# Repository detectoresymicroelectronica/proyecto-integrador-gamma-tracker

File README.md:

# Gamma Tracker
### Sonda gamma para cirugía radioguiada

<p>
Sistema de detección de radiación gamma para asistencia en cirugía laparoscópica oncológica, basado en <strong>centellador inorgánico + SiPM</strong>, con electrónica de lectura multicanal e interfaz en tiempo real.
</p>

<hr>

<p>
<strong>PROYECTO INTEGRADOR</strong><br>
Ingeniería en Telecomunicaciones · Instituto Balseiro · 2026–2027
</p>

<p>
<strong>Autor:</strong> Dana E. González<br>
<strong>Director:</strong> José Lipovetzky<br>
<strong>Codirector:</strong> Fabricio Alcalde
</p>

---

## Contexto

Este proyecto continúa y extiende el trabajo de la tesis *Gamma Tracker* (Torletti, 2025), que demostró la viabilidad de una sonda gamma portátil basada en centellador + SiPM para localización de tejido tumoral marcado con FDG (TRL 4–5). El dispositivo se encuentra en proceso de patentamiento ante el INPI.

El presente proyecto integrador busca avanzar hacia un sistema de mayor resolución espacial y espectral, abordando cuatro líneas principales:

* **Nuevo fotosensor:** evaluación de SiPMs de mayor área activa y menor tensión de polarización, con capacidad de espectroscopía de altura de pulso para discriminación energética a 511 keV.
* **Acople óptico:** comparación cuantitativa de técnicas (grasa óptica, adhesivos UV, fibra óptica) para optimizar eficiencia de transferencia de luz y estabilidad mecánica.
* **Sistema multipixel:** diseño de una matriz de centelladores acoplados a un arreglo de SiPMs con lectura multicanal para mapeo espacial de actividad gamma en tiempo real.
* **Electrónica e interfaz:** desarrollo de electrónica de adquisición, comunicación inalámbrica y alimentación por baterías, aptas para entorno quirúrgico (objetivo TRL 5–6).

---

## Estructura del repositorio

```text
logs/               Cuaderno de laboratorio digital (un archivo por sesión) + criterios/guias/instrucciones
scripts/
  ├── read/         Control de instrumentos y lectura
  └── analysis/     Post-procesamiento, comparación y visualización
data/               Datos experimentales organizados por campaña
  └── <campaña>/
      ├── raw/      CSV crudos (inmutables)
      └── graphs/   Curvas de los resultados
hardware/           Diseños de PCB (KiCad), uno por placa
  └── EVB-TIA-v0/
      └── fab/      Archivos de fabricación enviados (Gerber, BOM, CPL)
docs/               Documentación de soporte e imágenes de los logs
```

## 📓 Cuaderno de laboratorio

> El directorio `logs/` funciona como **cuaderno de laboratorio digital** del proyecto. Cada archivo registra una sesión de trabajo con objetivo, configuración experimental, observaciones, resultados, decisiones técnicas y pendientes. Tambien se incluyen documentos que sustenten las decisiones experimentales.
>
> Los logs priorizan **trazabilidad y reproducibilidad** por sobre presentación. Todo se registra en el cuaderno, preservando el historial completo del razonamiento experimental. 
>
> ```
> logs/
>  ├── 1 LOG — Lunes 3 de agosto de 2026.md
>  ├── 2 LOG — Lunes 10 de agosto de 2026.md
>  └── ...
> ```

---

## Progreso del proyecto

### Hitos

- **Hito 1 — Validación de SiPMs MICROFC-60035-SMT** (11/08/2026) — dispersión de V_br intra-lote σ ≈ 20 mV, ~100× menor que el modelo del prototipo anterior. Los 10 dispositivos son aptos para la matriz multipixel. Habilita la primera propuesta del PI.
- **Hito 2 — Primeros pulsos de fotón individual** (09/09/2026) — dark counts observados con la placa amplificadora BGA614 ×100 (SiPM #09). Primera vez que la cadena SiPM → amplificador → osciloscopio funciona en el proyecto.
- **Hito 3 — EVB-TIA v0 enviada a fabricar** (20/10/2026) — primera placa propia: TIA de una etapa con ADA4895 sobre la salida estándar del SiPM, con banco de R_F configurable por jumpers (159 Ω – 2,2 kΩ). 5 placas ensambladas en JLCPCB, con el SiPM soldado por reflujo.

### Registro semanal

**Semana del 03/08/2026**
- Setup de medición I-V validado (Keithley 2450 + pyvisa + script Python)
- Protocolo de conexión y seguridad definido 

**Semana del 10/08/2026**
- Caracterización I-V de los 10 SiPMs completada 
- Se confirmó offset de V_br entre lotes (~141 mV) 
- **→ Hito 1 alcanzado**

**Semana del 17/08/2026**
- Primer diseño en KiCad: placa breakout para el SiPM (fresada en CNC)

**Semana del 24/08/2026**
- Corriente oscura de los 10 SiPMs a V_ov = 2,5 V
- Plan del banco térmico (Peltier + watercooling + DS18B20)
- SiPM #05 destruido al soldarlo → protocolo de soldadura (≤ 260 °C, ≤ 10 s)

**Semana del 31/08/2026**
- Demostrado que el 60035 no se puede leer sin amplificación (3400 pF → ~0,14 mV/PE)

**Semana del 07/09/2026**
- Pulsos de fotón individual con la placa BGA614 ×100
- **→ Hito 2 alcanzado**

**Semana del 14/09/2026**
- Arduino + DS18B20 validado; Peltier nueva probada
- Comparación de topologías de amplificación (BGA614, TIA, amplificador inversor)

**Semana del 21/09/2026**
- Simulación del TIA de una etapa (ADA4895, Configuración C) y definición del banco de R_F

**Semanas del 05/10 y 12/10/2026**
- Diseño de la EVB-TIA v0 en KiCad: esquemático, layout, plano de masa, serigrafía (DRC 0/0/0)

**Semana del 19/10/2026**
- Archivos de fabricación y pedido a JLCPCB
- **→ Hito 3 alcanzado**

**Semana del 26/10/2026** *(próxima)*
- Banco térmico: reparar el conmutador de la Peltier y medir dV_br/dT
- Preparar la cadena de medición para la EVB-TIA (adquisición con osciloscopio, análisis de SPE)

---

## Convenciones

**Datos:** `{modelo}_{numero}_{YYYYMMDD}.csv`<br>
**Logs:** `N LOG — Día D de mes de AAAA.md`<br>
**Dispositivos:** `MFC60035_XX` (numeración secuencial por orden de medición)

---

## Instrumentación

| Equipo              | Modelo                                      | Interfaz              |
| ------------------- | ------------------------------------------- | --------------------- |
| Source Measure Unit | Keithley 2450                               | USB / SCPI vía PyVISA |
| Osciloscopio        | Keysight InfiniiVision DSOX3104T (1 GHz)    | —                     |
| Osciloscopio        | Rigol DS1204B (200 MHz)                     | —                     |
| Sensor de temperatura | DS18B20 + Arduino UNO                     | 1-Wire / serial       |
| Celda Peltier       | TEC1-12706                                  | —                     |
| SiPMs bajo prueba   | onsemi MicroFC-60035-SMT (C-Series, 6×6 mm) | —                     |

---

## Dependencias

* Python 3.11+
* PyVISA + backend pyvisa-py
* NumPy, Matplotlib, SciPy
* Arduino IDE: librerías OneWire y DallasTemperature
* KiCad 10 (diseño de PCB) y LTspice (simulación)

---

###  Casualties:

**Componentes destruidos:** `1`  
**Días sin quemar algo:** `56`

> 🫡 

---

## Documentación relacionada

* Torletti (2025). *Gamma Tracker: instrumentación para la detección de radiación gamma en cirugía laparoscópica.* Instituto Balseiro.
* Knoll (2010). *Radiation Detection and Measurement.* 4th ed., Wiley.
* onsemi. *C-Series SiPM Datasheet* — MicroFC-60035-SMT.
* onsemi. *AND9782/D — Biasing and Readout of onsemi SiPM Sensors.*
* onsemi. *AND9788/D — Handling and Soldering of Molded Leadframe Packaged SiPM Sensors.*
* Analog Devices. *ADA4895-1/-2 Data Sheet.*
* Keithley. *Model 2450 SourceMeter SMU — Reference Manual.*

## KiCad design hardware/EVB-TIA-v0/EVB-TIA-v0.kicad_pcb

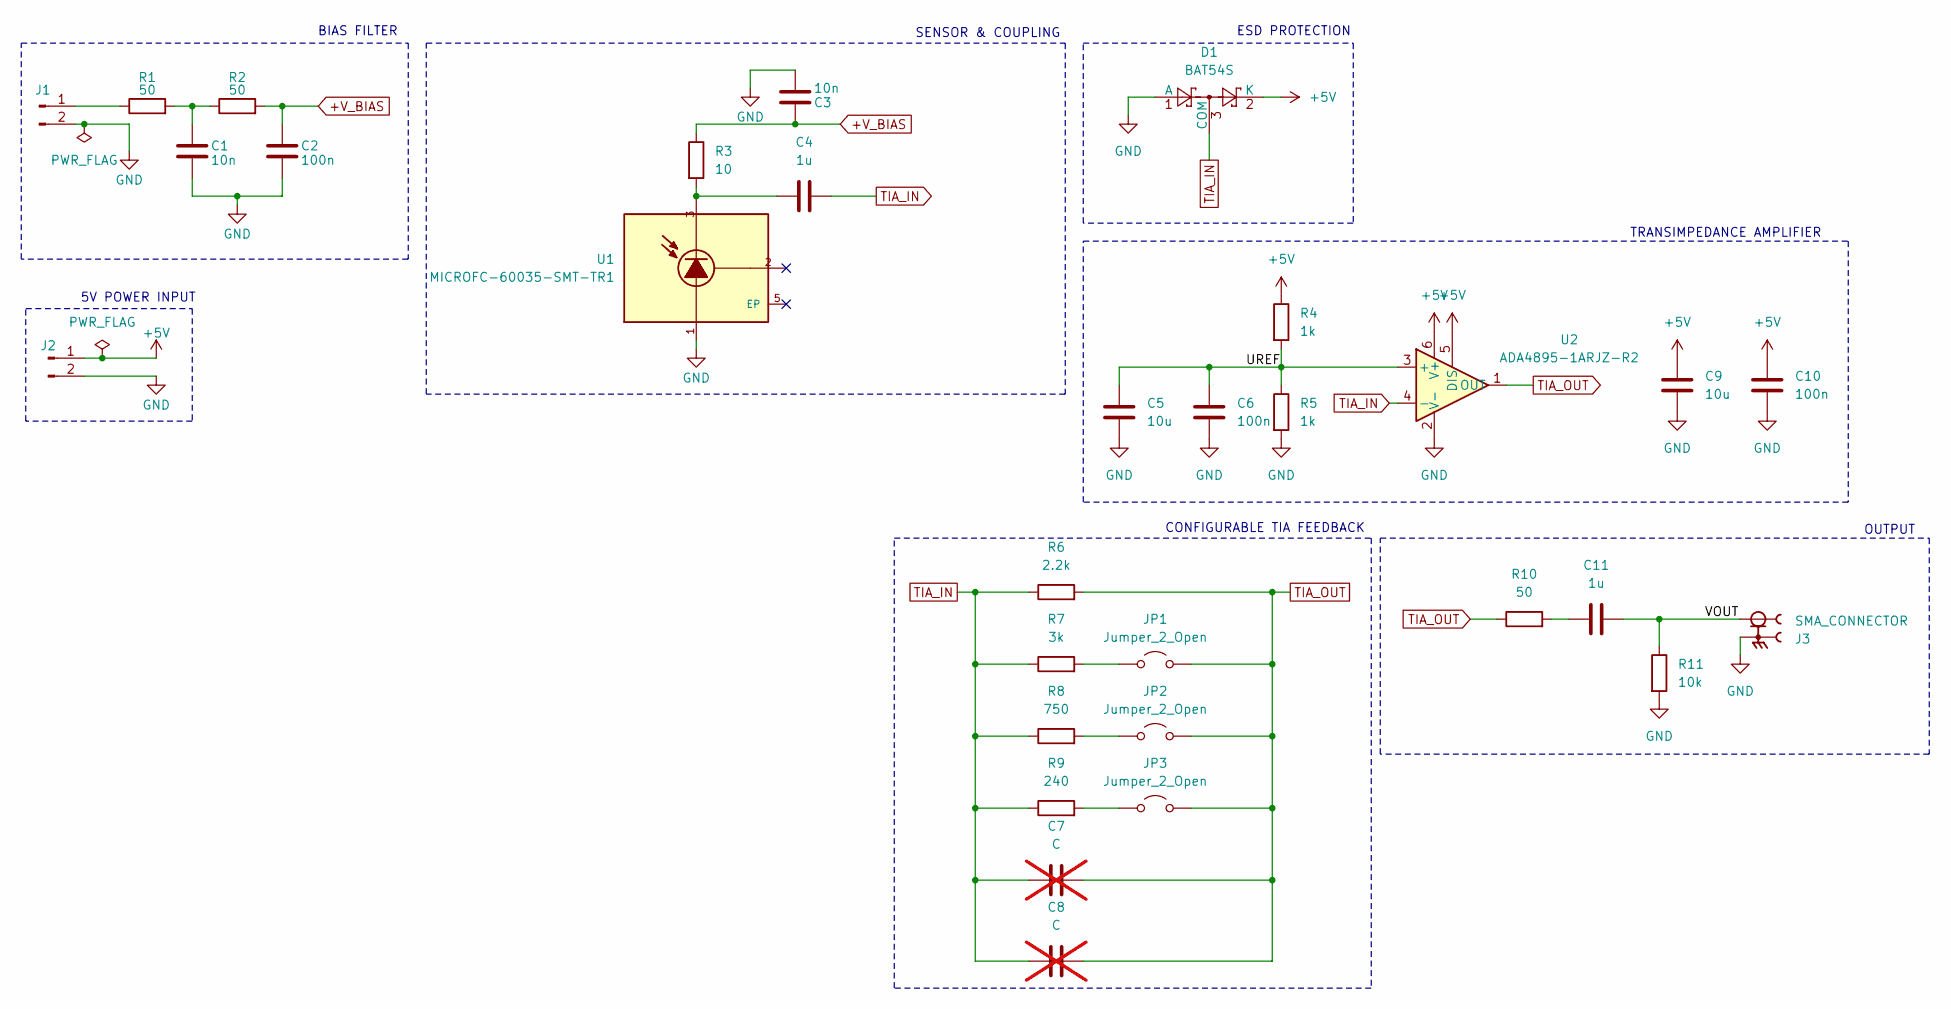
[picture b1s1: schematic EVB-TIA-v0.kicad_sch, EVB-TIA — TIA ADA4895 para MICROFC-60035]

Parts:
C1, C3: 10n; C_0805_2012Metric
C2, C6, C10: 100n; C_0805_2012Metric
C4: 1u; C_1206_3216Metric
C5, C9: 10u; C_0805_2012Metric
C7, C8: C; C_0603_1608Metric_Pad1.08x0.95mm_HandSolder; not fitted
C11: 1u; C_0805_2012Metric
D1: BAT54S; SOT-23
J1, J2: Conn_01x02_Pin; PinHeader_1x02_P2.54mm_Vertical
J3: SMA_CONNECTOR; LPRS_SMA_CONNECTOR_ANCHITO; PARTREV 1.3
JP1, JP2, JP3: Jumper_2_Open; PinHeader_1x02_P2.54mm_Vertical
R1, R2, R10: 50; R_0603_1608Metric
R3: 10; R_0603_1608Metric
R4, R5: 1k; R_0603_1608Metric
R6: 2.2k; R_0603_1608Metric
R7: 3k; R_0603_1608Metric
R8: 750; R_0603_1608Metric
R9: 240; R_0603_1608Metric
R11: 10k; R_0603_1608Metric
U1: MICROFC-60035-SMT-TR1; XDCR_MICROFC-60035-SMT-TR1; PARTREV 31 JUL 2018; LCSC C905854
U2: ADA4895-1ARJZ-R2; SOT-23-6; LCSC C654293

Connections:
+5V: C9.1, C10.1, D1.2 (K), J2.1, R4.1, U2.5 (DIS), U2.6 (V+)
+V_BIAS: C2.1, C3.1, R2.2, R3.1
/UREF: C5.1, C6.1, R4.2, R5.1, U2.3 (+)
/VOUT: C11.2, J3.1, R11.1
GND: C1.2, C2.2, C3.2, C5.2, C6.2, C9.2, C10.2, D1.1 (A), J1.2, J2.2, J3.G1, J3.G2, J3.G3, J3.G4, R5.2, R11.2, U1.1, U2.2 (V-)
unnamed: C1.1, R1.2, R2.1
unnamed: C4.1, R3.2, U1.3
unnamed: C11.1, R10.2
unnamed: J1.1, R1.1
unnamed: JP1.1 (A), R7.2
unnamed: JP2.1 (A), R8.2
unnamed: JP3.1 (A), R9.2
TIA_IN: C4.2, C7.1, C8.1, D1.3 (COM), R6.1, R7.1, R8.1, R9.1, U2.4 (-)
TIA_OUT: C7.2, C8.2, JP1.2 (B), JP2.2 (B), JP3.2 (B), R6.2, R10.1, U2.1 (OUT)

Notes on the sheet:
ESD PROTECTION
OUTPUT
CONFIGURABLE TIA FEEDBACK
BIAS FILTER
5V POWER INPUT
TRANSIMPEDANCE AMPLIFIER
SENSOR & COUPLING

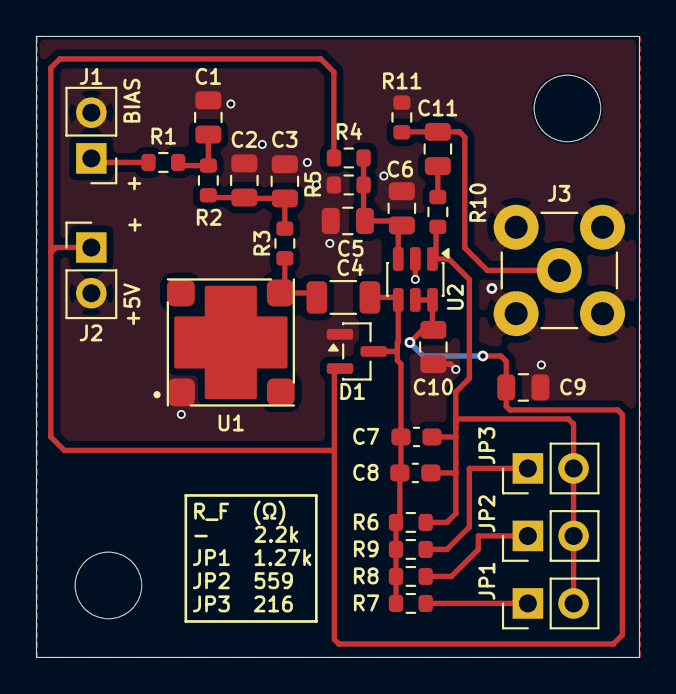
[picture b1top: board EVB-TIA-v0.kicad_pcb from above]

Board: 2 copper layers, 33.5 x 34.5 mm, 33 parts (0 on the bottom side), 14 nets.

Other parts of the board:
H1, H2: MountingHole_3.7mm

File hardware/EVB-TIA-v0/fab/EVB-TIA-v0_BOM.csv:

"Designator","Comment","Footprint","LCSC Part #"
"C1,C3","10n","Capacitor_SMD:C_0805_2012Metric",""
"C2,C6,C10","100n","Capacitor_SMD:C_0805_2012Metric",""
"C4","1u","Capacitor_SMD:C_1206_3216Metric",""
"C5,C9","10u","Capacitor_SMD:C_0805_2012Metric",""
"C11","1u","Capacitor_SMD:C_0805_2012Metric",""
"D1","BAT54S","Package_TO_SOT_SMD:SOT-23",""
"R1,R2,R10","50","Resistor_SMD:R_0603_1608Metric",""
"R3","10","Resistor_SMD:R_0603_1608Metric",""
"R4,R5","1k","Resistor_SMD:R_0603_1608Metric",""
"R6","2.2k","Resistor_SMD:R_0603_1608Metric",""
"R7","3k","Resistor_SMD:R_0603_1608Metric",""
"R8","750","Resistor_SMD:R_0603_1608Metric",""
"R9","240","Resistor_SMD:R_0603_1608Metric",""
"R11","10k","Resistor_SMD:R_0603_1608Metric",""
"U1","MICROFC-60035-SMT-TR1","EVB-TIA:XDCR_MICROFC-60035-SMT-TR1","C905854"
"U2","ADA4895-1ARJZ-R2","Package_TO_SOT_SMD:SOT-23-6","C654293"
